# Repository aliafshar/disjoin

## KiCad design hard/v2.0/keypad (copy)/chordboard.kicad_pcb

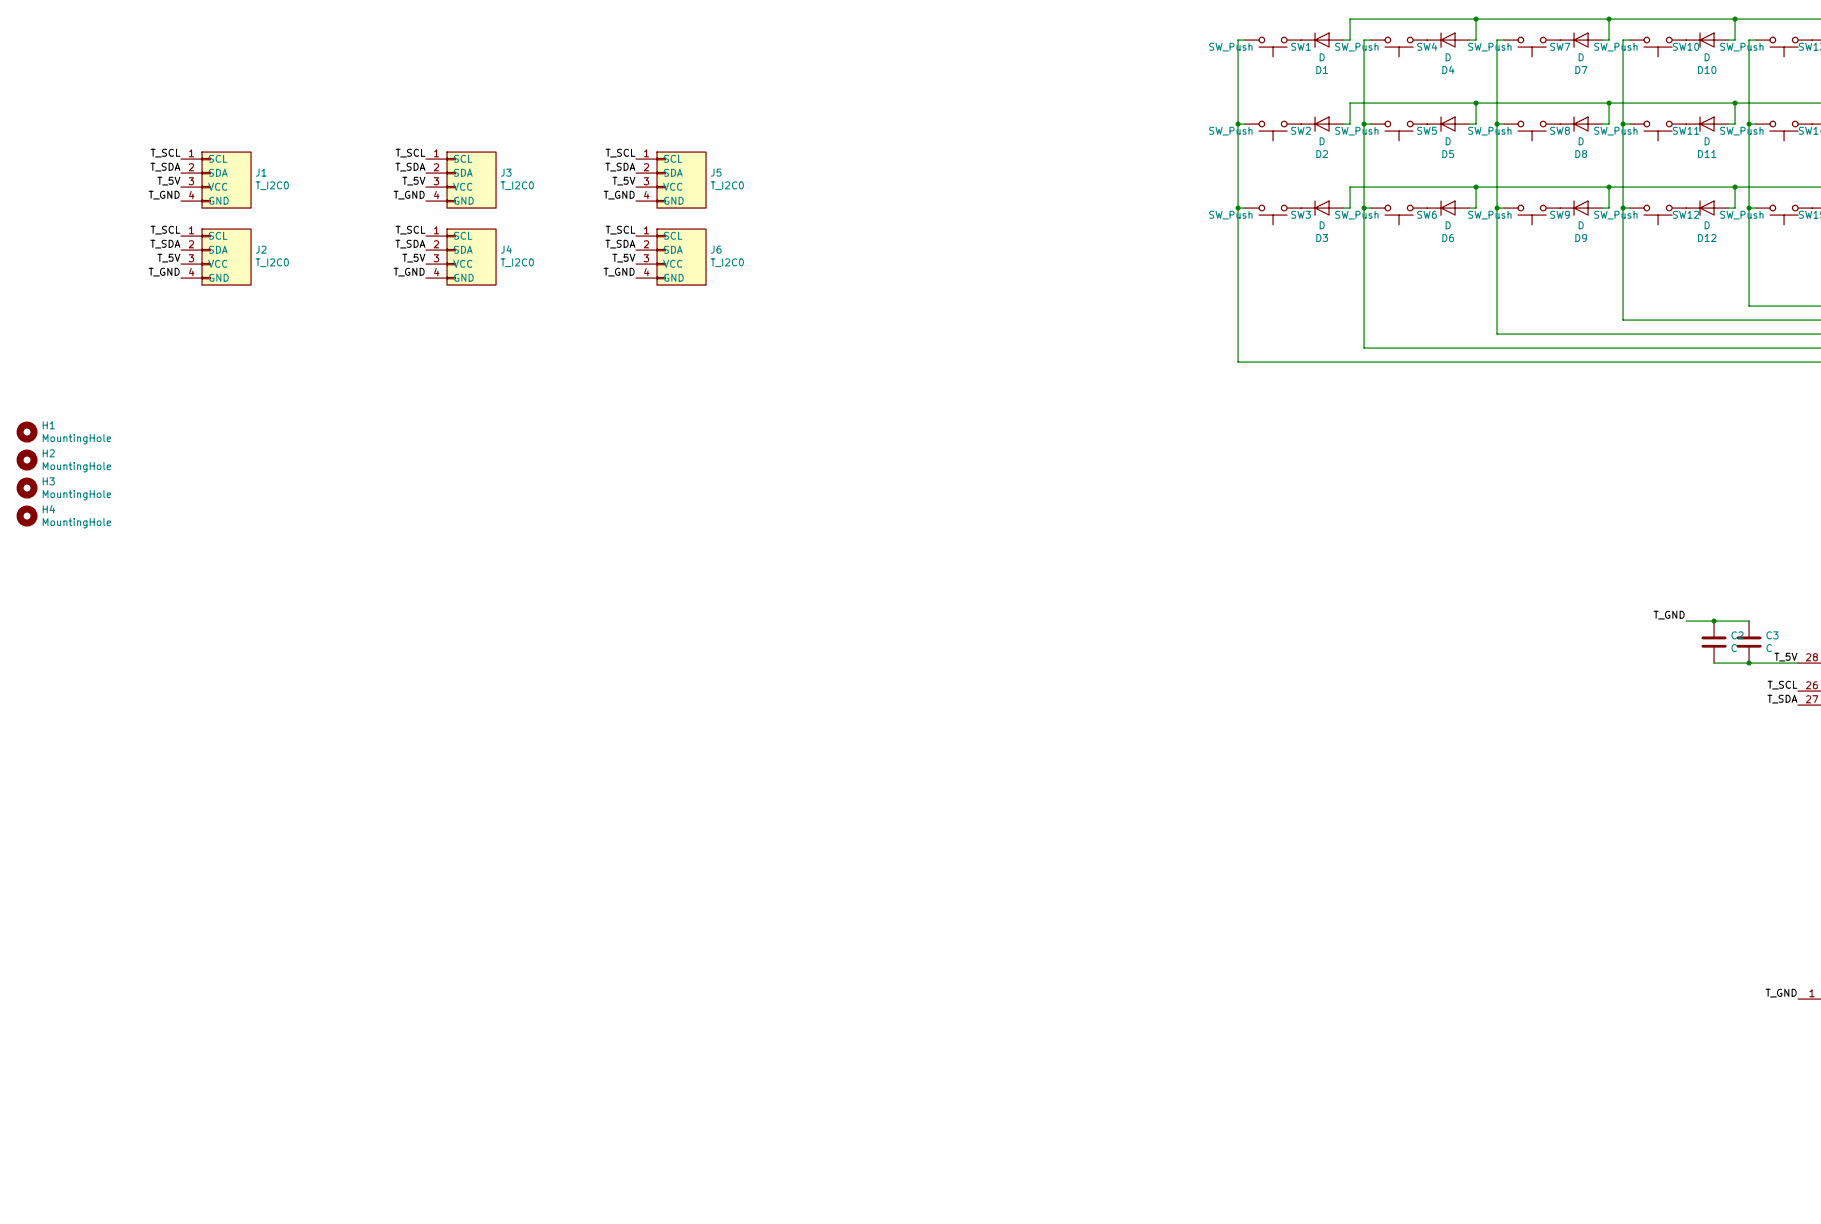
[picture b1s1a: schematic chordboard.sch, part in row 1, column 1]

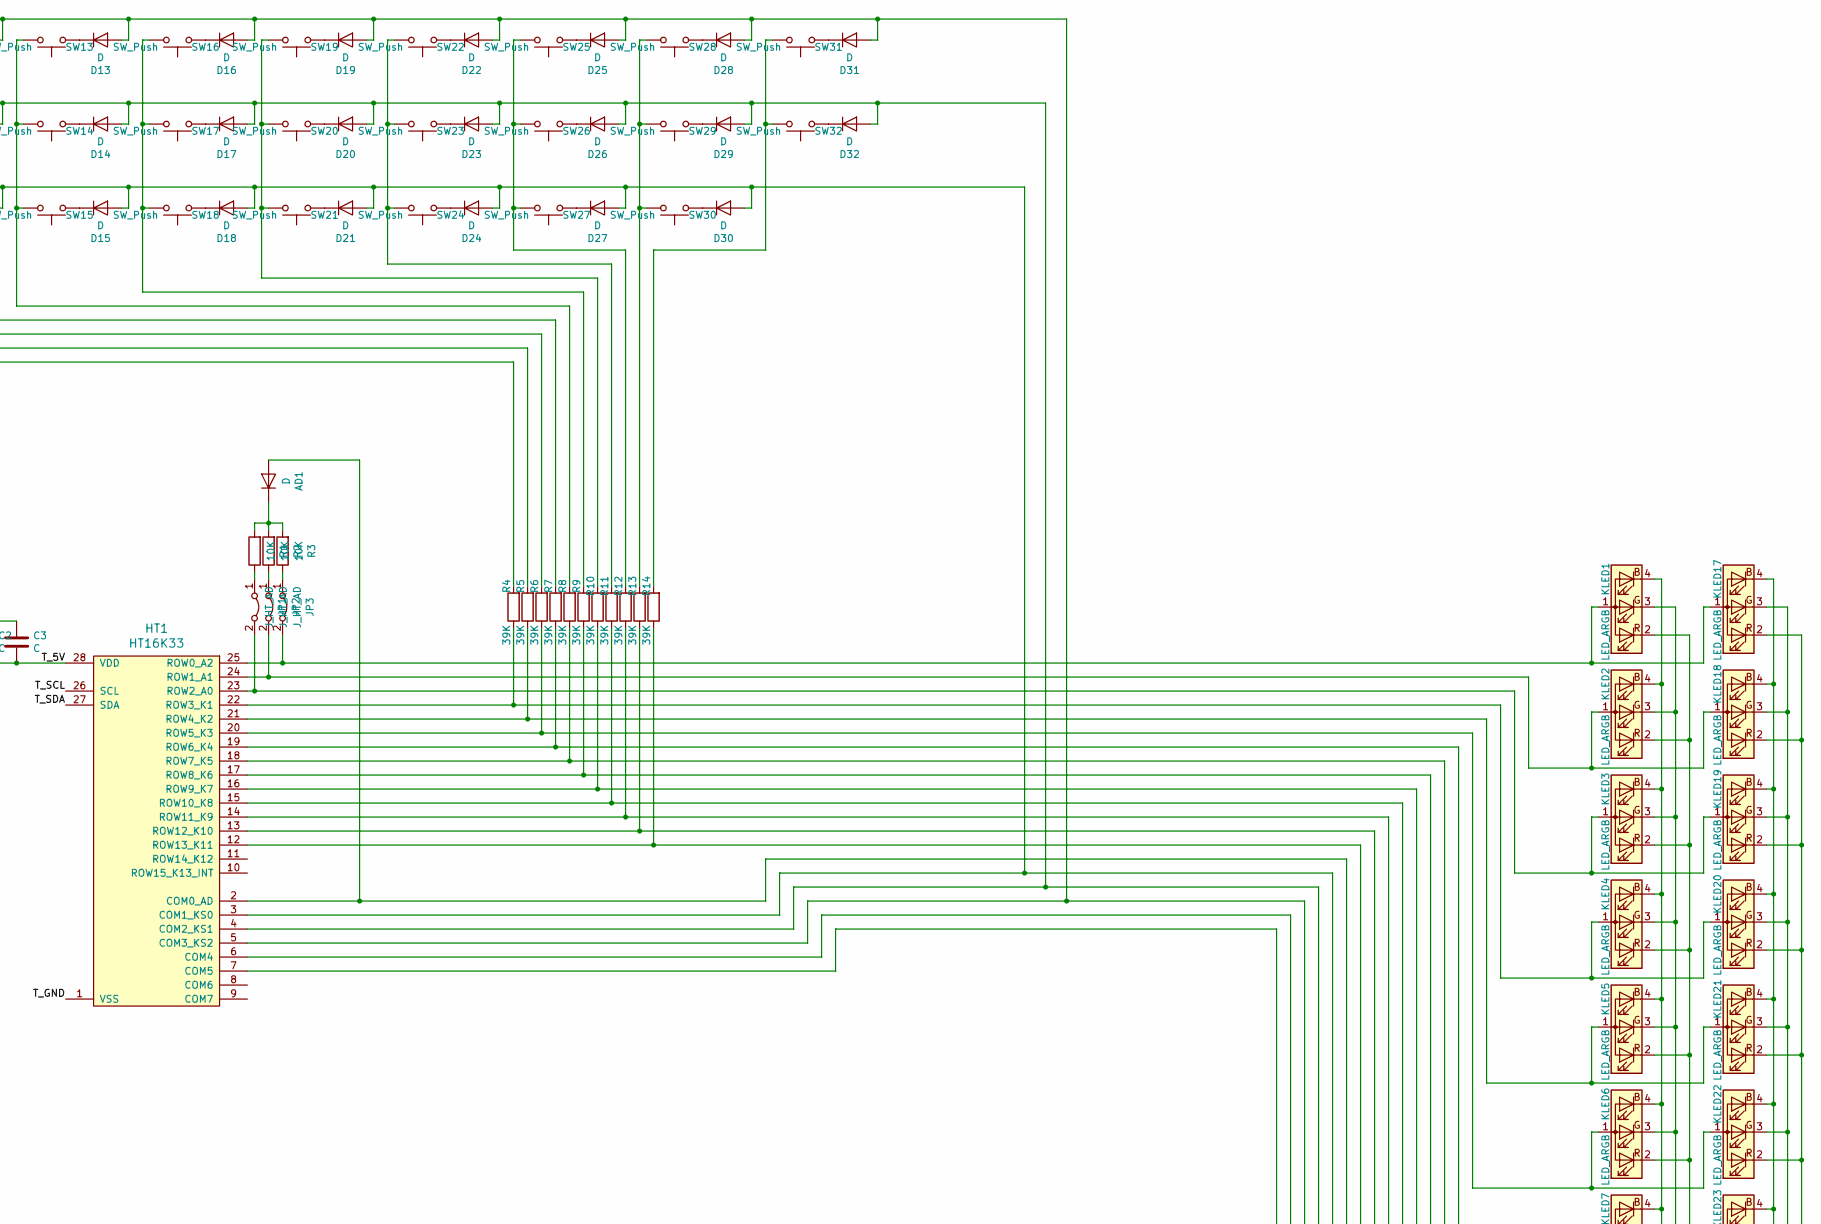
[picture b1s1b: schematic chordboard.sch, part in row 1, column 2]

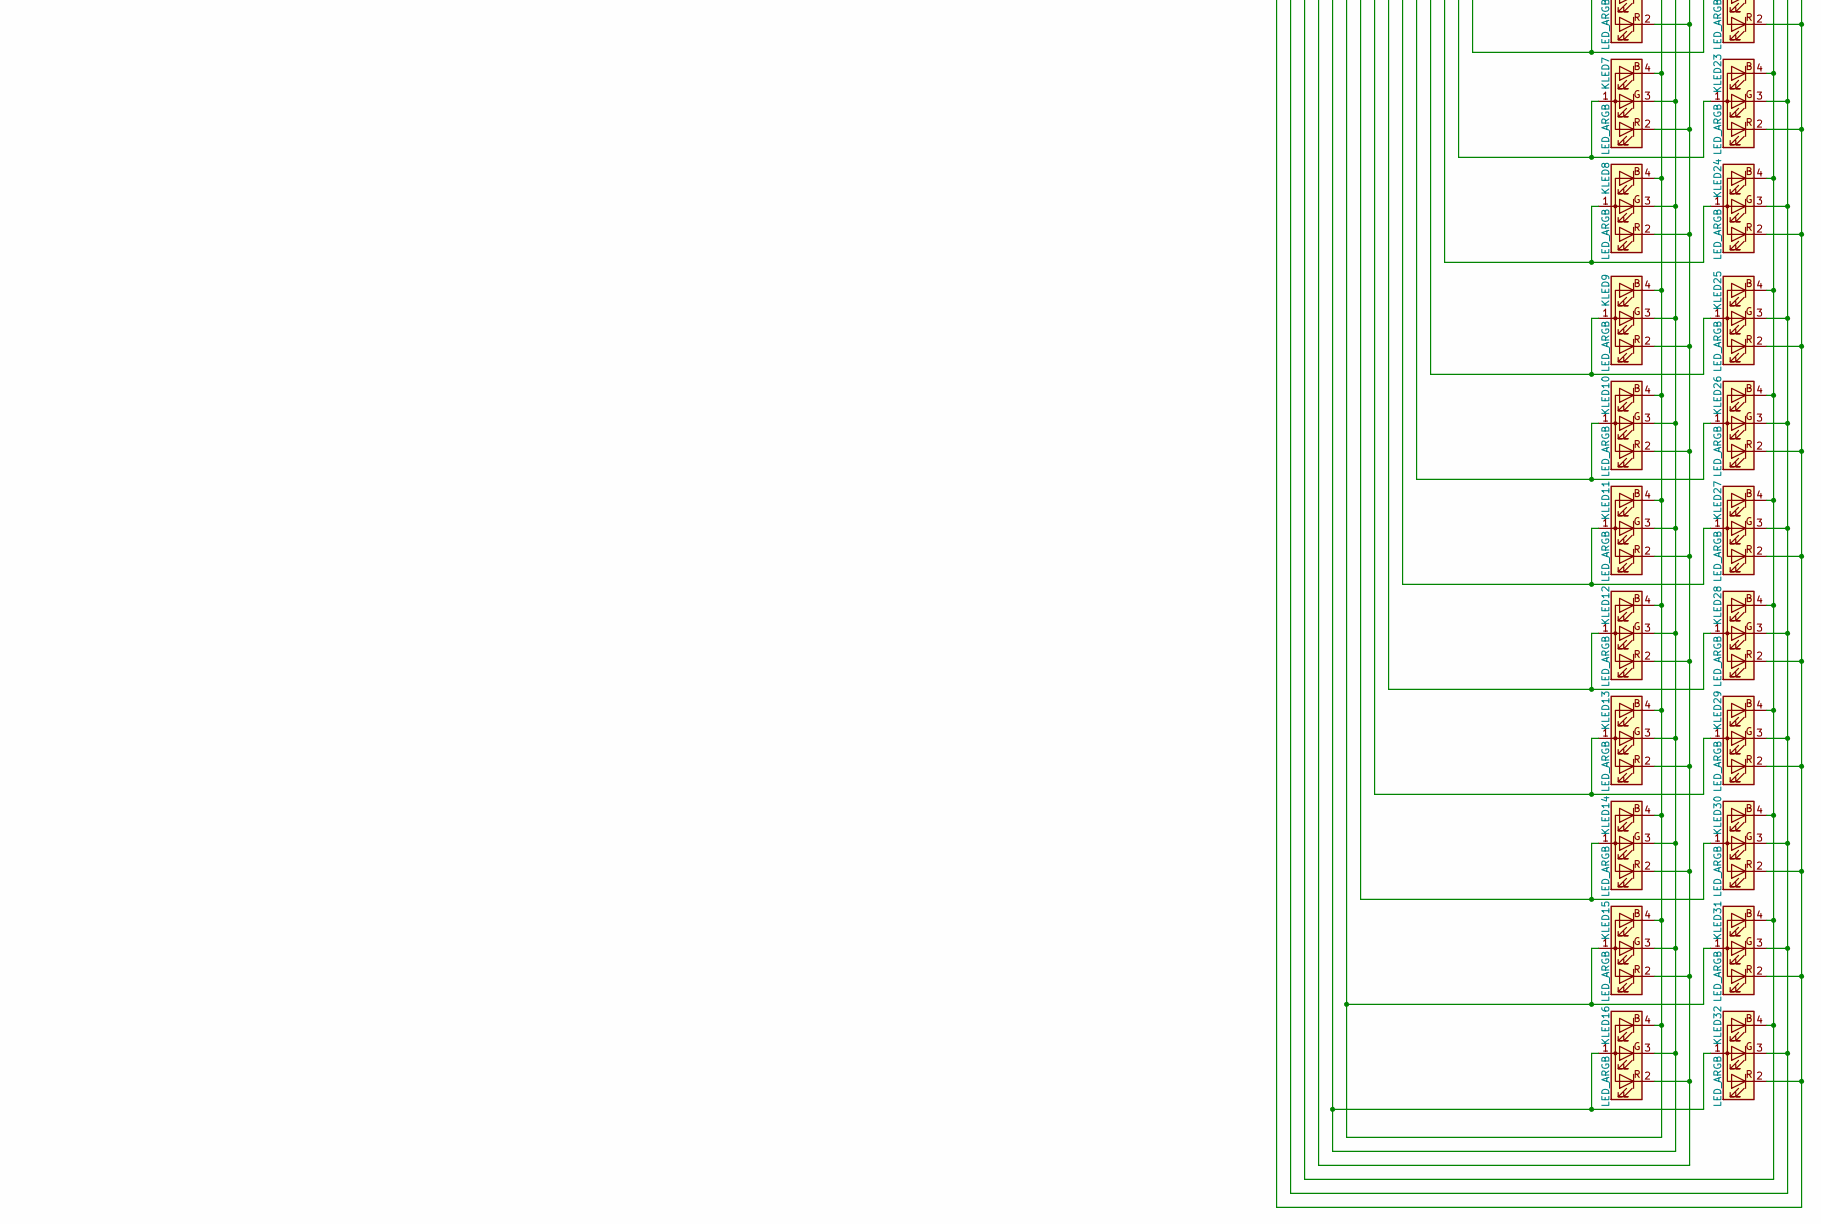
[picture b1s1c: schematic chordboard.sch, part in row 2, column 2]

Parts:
AD1: D; D_DO-41_SOD81_P7.62mm_Horizontal
C2, C3: C; C_Disc_D3.4mm_W2.1mm_P2.50mm
D1, D2, D3, D4, D5, D6, D7, D8, D9, D10, D11, D12, D13, D14, D15, D16, D17, D18, D19, D20, D21, D22, D23, D24, D25, D26, D27, D28, D29, D30, D31, D32: D; D_DO-41_SOD81_P7.62mm_Horizontal
H1, H2, H3, H4: MountingHole; MountingHole_2.7mm_M2.5_Pad_Via
HT1: HT16K33; SOIC-28W_7.5x17.9mm_P1.27mm
J1, J2, J3, J4: T_I2C0; JST_PH_B4B-PH-K_1x04_P2.00mm_Vertical
J5, J6: T_I2C0; PinHeader_1x04_P2.54mm_Vertical
JP1, JP2, JP3: J_HT_AD; SolderJumper-2_P1.3mm_Open_Pad1.0x1.5mm
KLED1, KLED2, KLED3, KLED4, KLED5, KLED6, KLED7, KLED8, KLED9, KLED10, KLED11, KLED12, KLED13, KLED14, KLED15, KLED16, KLED17, KLED18, KLED19, KLED20, KLED21, KLED22, KLED23, KLED24, KLED25, KLED26, KLED27, KLED28, KLED29, KLED30, KLED31, KLED32: LED_ARGB; LED_D3.0mm-4
R1, R2, R3: 10K; R_Axial_DIN0204_L3.6mm_D1.6mm_P5.08mm_Horizontal
R4, R5, R6, R7, R8, R9, R10, R11, R12, R13, R14: 39K; R_Axial_DIN0204_L3.6mm_D1.6mm_P5.08mm_Horizontal
SW1, SW2, SW3, SW4, SW5, SW6, SW7, SW8, SW9, SW10, SW11, SW12, SW13, SW14, SW15, SW16, SW17, SW18, SW19, SW20, SW21, SW22, SW23, SW24, SW25, SW26, SW27, SW28, SW29, SW30, SW31, SW32: SW_Push; CHERRY_PCB_100H

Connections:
/T_5V: C2.2, C3.2, HT1.28 (VDD), J1.3 (VCC), J2.3 (VCC), J3.3 (VCC), J4.3 (VCC), J5.3 (VCC), J6.3 (VCC)
/T_GND: C2.1, C3.1, HT1.1 (VSS), J1.4 (GND), J2.4 (GND), J3.4 (GND), J4.4 (GND), J5.4 (GND), J6.4 (GND)
/T_SCL: HT1.26 (SCL), J1.1 (SCL), J2.1 (SCL), J3.1 (SCL), J4.1 (SCL), J5.1 (SCL), J6.1 (SCL)
/T_SDA: HT1.27 (SDA), J1.2 (SDA), J2.2 (SDA), J3.2 (SDA), J4.2 (SDA), J5.2 (SDA), J6.2 (SDA)
unnamed: AD1.1 (K), R1.2, R2.2, R3.2
unnamed: AD1.2 (A), HT1.2 (COM0_AD), KLED1.4 (BK), KLED2.4 (BK), KLED3.4 (BK), KLED4.4 (BK), KLED5.4 (BK), KLED6.4 (BK), KLED7.4 (BK), KLED8.4 (BK), KLED9.4 (BK), KLED10.4 (BK), KLED11.4 (BK), KLED12.4 (BK), KLED13.4 (BK), KLED14.4 (BK), KLED15.1 (A), KLED15.4 (BK), KLED16.4 (BK), KLED31.1 (A)
unnamed: D1.1 (K), SW1.1
unnamed: D1.2 (A), D4.2 (A), D7.2 (A), D10.2 (A), D13.2 (A), D16.2 (A), D19.2 (A), D22.2 (A), D25.2 (A), D28.2 (A), D31.2 (A), HT1.5 (COM3_KS2), KLED17.4 (BK), KLED18.4 (BK), KLED19.4 (BK), KLED20.4 (BK), KLED21.4 (BK), KLED22.4 (BK), KLED23.4 (BK), KLED24.4 (BK), KLED25.4 (BK), KLED26.4 (BK), KLED27.4 (BK), KLED28.4 (BK), KLED29.4 (BK), KLED30.4 (BK), KLED31.4 (BK), KLED32.4 (BK)
unnamed: D2.1 (K), SW2.1
unnamed: D3.1 (K), SW3.1
unnamed: D4.1 (K), SW4.1
unnamed: D5.1 (K), SW5.1
unnamed: D6.1 (K), SW6.1
unnamed: D7.1 (K), SW7.1
unnamed: D8.1 (K), SW8.1
unnamed: D9.1 (K), SW9.1
unnamed: D10.1 (K), SW10.1
unnamed: D11.1 (K), SW11.1
unnamed: D2.2 (A), D5.2 (A), D8.2 (A), D11.2 (A), D14.2 (A), D17.2 (A), D20.2 (A), D23.2 (A), D26.2 (A), D29.2 (A), D32.2 (A), HT1.4 (COM2_KS1), KLED1.2 (RK), KLED2.2 (RK), KLED3.2 (RK), KLED4.2 (RK), KLED5.2 (RK), KLED6.2 (RK), KLED7.2 (RK), KLED8.2 (RK), KLED9.2 (RK), KLED10.2 (RK), KLED11.2 (RK), KLED12.2 (RK), KLED13.2 (RK), KLED14.2 (RK), KLED15.2 (RK), KLED16.2 (RK)
unnamed: D12.1 (K), SW12.1
unnamed: D3.2 (A), D6.2 (A), D9.2 (A), D12.2 (A), D15.2 (A), D18.2 (A), D21.2 (A), D24.2 (A), D27.2 (A), D30.2 (A), HT1.3 (COM1_KS0), KLED1.3 (GK), KLED2.3 (GK), KLED3.3 (GK), KLED4.3 (GK), KLED5.3 (GK), KLED6.3 (GK), KLED7.3 (GK), KLED8.3 (GK), KLED9.3 (GK), KLED10.3 (GK), KLED11.3 (GK), KLED12.3 (GK), KLED13.3 (GK), KLED14.3 (GK), KLED15.3 (GK), KLED16.1 (A), KLED16.3 (GK), KLED32.1 (A)
unnamed: D13.1 (K), SW13.1
unnamed: D14.1 (K), SW14.1
unnamed: D15.1 (K), SW15.1
unnamed: D16.1 (K), SW16.1
unnamed: D17.1 (K), SW17.1
unnamed: D18.1 (K), SW18.1
unnamed: D19.1 (K), SW19.1
unnamed: D20.1 (K), SW20.1
unnamed: D21.1 (K), SW21.1
unnamed: D22.1 (K), SW22.1
unnamed: D23.1 (K), SW23.1
unnamed: D24.1 (K), SW24.1
unnamed: D25.1 (K), SW25.1
unnamed: D26.1 (K), SW26.1
unnamed: D27.1 (K), SW27.1
unnamed: D28.1 (K), SW28.1
unnamed: D29.1 (K), SW29.1
unnamed: D30.1 (K), SW30.1
unnamed: D31.1 (K), SW31.1
unnamed: D32.1 (K), SW32.1
unnamed: HT1.6 (COM4), KLED17.3 (GK), KLED18.3 (GK), KLED19.3 (GK), KLED20.3 (GK), KLED21.3 (GK), KLED22.3 (GK), KLED23.3 (GK), KLED24.3 (GK), KLED25.3 (GK), KLED26.3 (GK), KLED27.3 (GK), KLED28.3 (GK), KLED29.3 (GK), KLED30.3 (GK), KLED31.3 (GK), KLED32.3 (GK)
unnamed: HT1.7 (COM5), KLED17.2 (RK), KLED18.2 (RK), KLED19.2 (RK), KLED20.2 (RK), KLED21.2 (RK), KLED22.2 (RK), KLED23.2 (RK), KLED24.2 (RK), KLED25.2 (RK), KLED26.2 (RK), KLED27.2 (RK), KLED28.2 (RK), KLED29.2 (RK), KLED30.2 (RK), KLED31.2 (RK), KLED32.2 (RK)
unnamed: HT1.12 (ROW13_K11), KLED14.1 (A), KLED30.1 (A), R14.1
unnamed: HT1.13 (ROW12_K10), KLED13.1 (A), KLED29.1 (A), R13.1
unnamed: HT1.14 (ROW11_K9), KLED12.1 (A), KLED28.1 (A), R12.1
unnamed: HT1.15 (ROW10_K8), KLED11.1 (A), KLED27.1 (A), R11.1
unnamed: HT1.16 (ROW9_K7), KLED10.1 (A), KLED26.1 (A), R10.1
unnamed: HT1.17 (ROW8_K6), KLED9.1 (A), KLED25.1 (A), R9.1
unnamed: HT1.18 (ROW7_K5), KLED8.1 (A), KLED24.1 (A), R8.1
unnamed: HT1.19 (ROW6_K4), KLED7.1 (A), KLED23.1 (A), R7.1
unnamed: HT1.20 (ROW5_K3), KLED6.1 (A), KLED22.1 (A), R6.1
unnamed: HT1.21 (ROW4_K2), KLED5.1 (A), KLED21.1 (A), R5.1
unnamed: HT1.22 (ROW3_K1), KLED4.1 (A), KLED20.1 (A), R4.1
unnamed: HT1.23 (ROW2_A0), JP1.2 (B), KLED3.1 (A), KLED19.1 (A)
unnamed: HT1.24 (ROW1_A1), JP2.2 (B), KLED2.1 (A), KLED18.1 (A)
unnamed: HT1.25 (ROW0_A2), JP3.2 (B), KLED1.1 (A), KLED17.1 (A)
unnamed: JP1.1 (A), R1.1
unnamed: JP2.1 (A), R2.1
unnamed: JP3.1 (A), R3.1
unnamed: R4.2, SW1.2, SW2.2, SW3.2
unnamed: R5.2, SW4.2, SW5.2, SW6.2
unnamed: R6.2, SW7.2, SW8.2, SW9.2
unnamed: R7.2, SW10.2, SW11.2, SW12.2
unnamed: R8.2, SW13.2, SW14.2, SW15.2
unnamed: R9.2, SW16.2, SW17.2, SW18.2
unnamed: R10.2, SW19.2, SW20.2, SW21.2
unnamed: R11.2, SW22.2, SW23.2, SW24.2
unnamed: R12.2, SW25.2, SW26.2, SW27.2
unnamed: R13.2, SW28.2, SW29.2, SW30.2
unnamed: R14.2, SW31.2, SW32.2

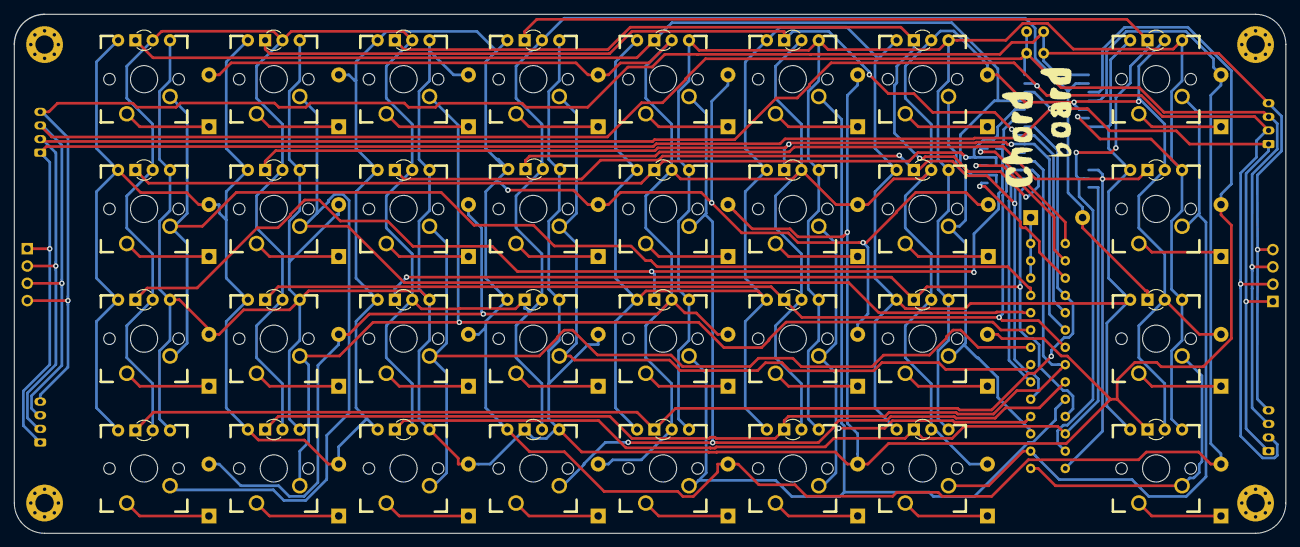
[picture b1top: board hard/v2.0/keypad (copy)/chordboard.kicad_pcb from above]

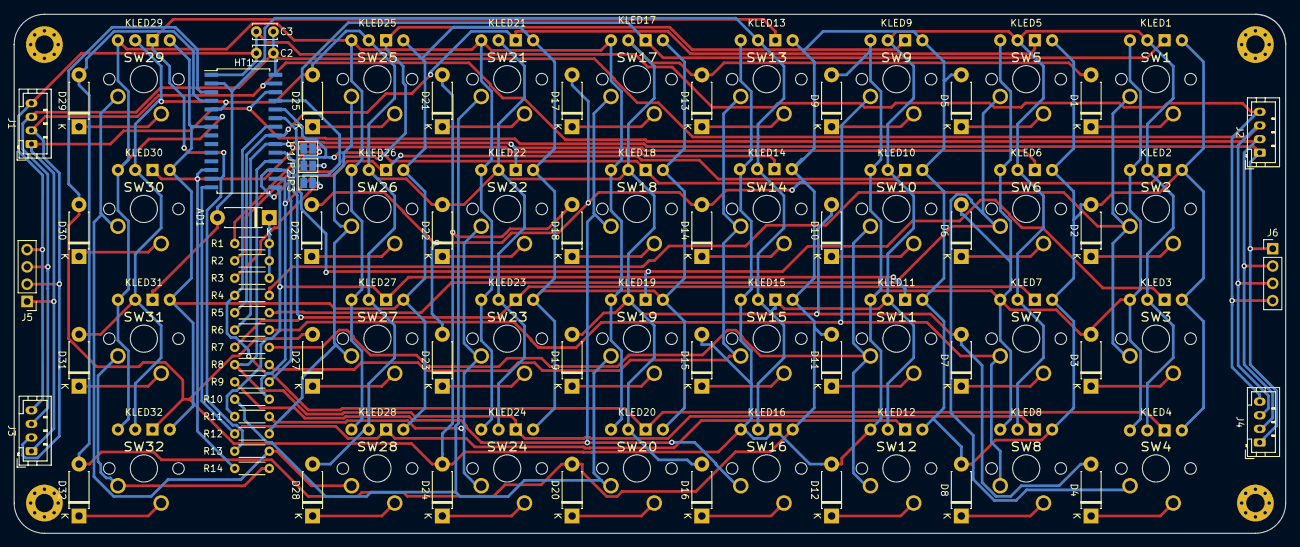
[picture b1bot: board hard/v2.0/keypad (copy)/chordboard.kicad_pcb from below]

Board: 2 copper layers, 186.7 x 76.2 mm, 127 parts (59 on the bottom side), 71 nets.

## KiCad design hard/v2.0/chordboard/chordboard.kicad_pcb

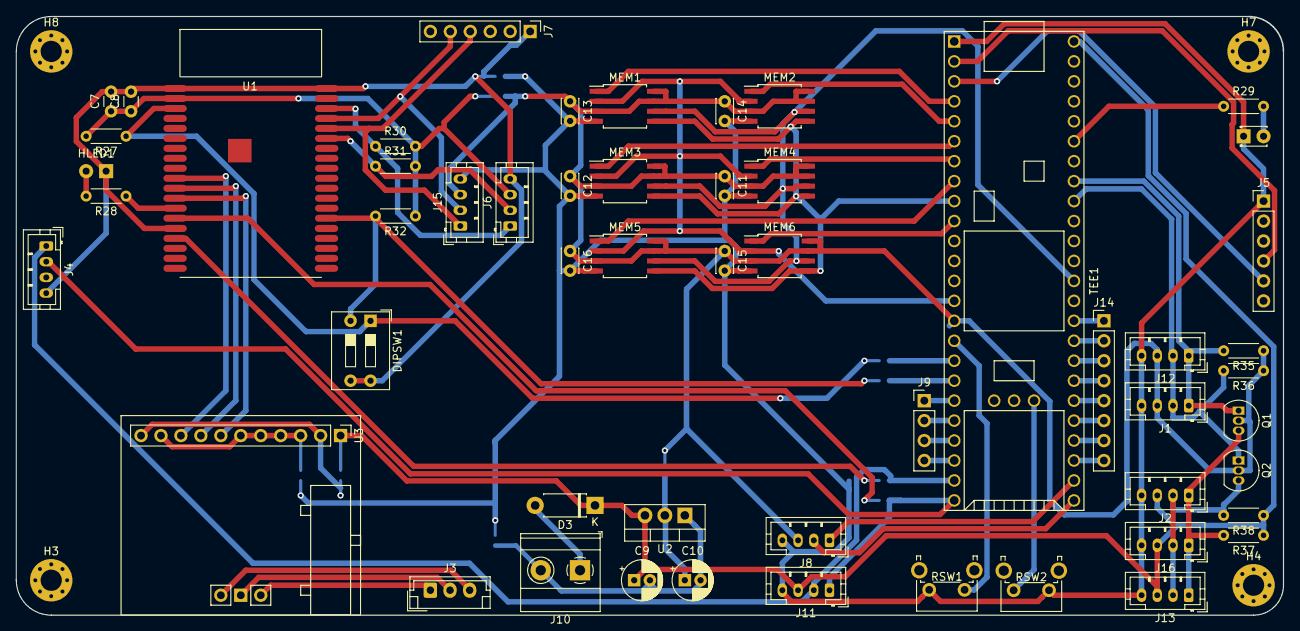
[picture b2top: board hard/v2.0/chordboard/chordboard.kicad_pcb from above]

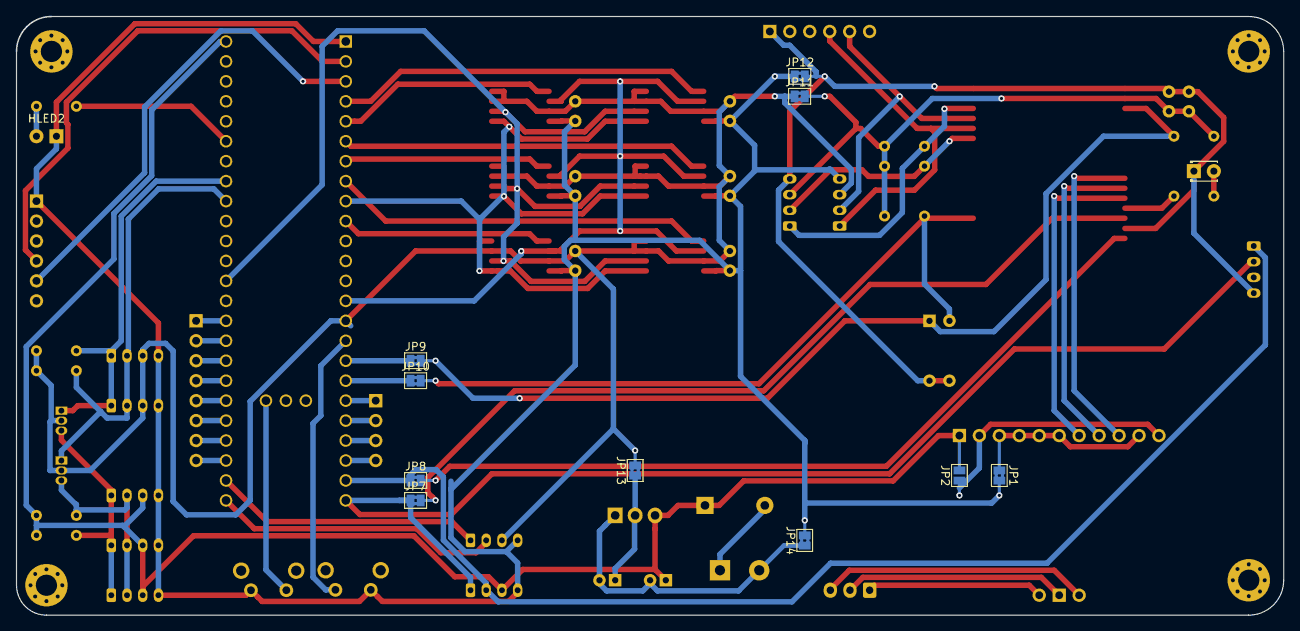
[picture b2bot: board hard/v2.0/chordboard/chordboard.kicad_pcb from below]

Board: 2 copper layers, 161.3 x 76.2 mm, 68 parts (11 on the bottom side), 63 nets.

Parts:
C7, C8: C; C_Disc_D3.0mm_W1.6mm_P2.50mm
C9: 10uF; CP_Radial_D5.0mm_P2.00mm
C10: 100uF; CP_Radial_D5.0mm_P2.00mm
C11, C12, C13, C14, C15, C16: C_Small; C_Disc_D3.0mm_W2.0mm_P2.50mm
D3: D; D_DO-41_SOD81_P7.62mm_Horizontal
DIPSW1: E_BOOTOPTS; SW_DIP_SPSTx02_Slide_9.78x7.26mm_W7.62mm_P2.54mm
H3, H4, H7, H8: MountingHole; MountingHole_2.7mm_M2.5_Pad_Via
HLED1: E_HEARTBEAT; LED_D1.8mm_W3.3mm_H2.4mm
HLED2: T_HEARTBEAT; LED_D1.8mm_W3.3mm_H2.4mm
J1, J12: T_I2C0_3V; JST_PH_B4B-PH-K_1x04_P2.00mm_Vertical
J2, J13, J16: T_I2C0_5V; JST_PH_B4B-PH-K_1x04_P2.00mm_Vertical
J3: Conn_01x03; JST_EH_B03B-EH-A_1x03_P2.50mm_Vertical
J4: E_UART2; JST_PH_B4B-PH-K_1x04_P2.00mm_Vertical
J5: T_UART0; PinHeader_1x06_P2.54mm_Vertical
J6: E_I2C0; JST_PH_B4B-PH-K_1x04_P2.00mm_Vertical
J7: E_UART0; PinHeader_1x06_P2.54mm_Vertical
J8: T_UART5; JST_PH_B4B-PH-K_1x04_P2.00mm_Vertical
J9: Conn_01x04; PinHeader_1x04_P2.54mm_Vertical
J10: ++5V_IN; TerminalBlock_Phoenix_MKDS-1,5-2_1x02_P5.00mm_Horizontal
J11: T_UART4; JST_PH_B4B-PH-K_1x04_P2.00mm_Vertical
J14: Conn_01x08; PinHeader_1x08_P2.54mm_Vertical
J15: E_UART1; JST_PH_B4B-PH-K_1x04_P2.00mm_Vertical
JP1, JP12: Jumper_2_Bridged; SolderJumper-2_P1.3mm_Bridged2Bar_Pad1.0x1.5mm
JP2: Jumper_2_Open; SolderJumper-2_P1.3mm_Open_Pad1.0x1.5mm
JP7: J_ESP_RX2; SolderJumper-2_P1.3mm_Bridged2Bar_Pad1.0x1.5mm
JP8: J_ESP_TX2; SolderJumper-2_P1.3mm_Bridged2Bar_Pad1.0x1.5mm
JP9: J_ESP_RST; SolderJumper-2_P1.3mm_Bridged2Bar_Pad1.0x1.5mm
JP10: J_ESP_D0; SolderJumper-2_P1.3mm_Bridged2Bar_Pad1.0x1.5mm
JP11: J_ESP_3V3; SolderJumper-2_P1.3mm_Bridged2Bar_Pad1.0x1.5mm
JP13: J_PWR_3V3; SolderJumper-2_P1.3mm_Bridged2Bar_Pad1.0x1.5mm
JP14: J_PWR_GND; SolderJumper-2_P1.3mm_Bridged2Bar_Pad1.0x1.5mm
MEM1, MEM2, MEM3, MEM4, MEM5, MEM6: 23LC1024; SOIJ-8_5.3x5.3mm_P1.27mm
Q1, Q2: 2N7000; TO-92_Inline
R27, R32: 10K; R_Axial_DIN0204_L3.6mm_D1.6mm_P5.08mm_Horizontal
R28, R29: 200; R_Axial_DIN0204_L3.6mm_D1.6mm_P5.08mm_Horizontal
R30, R31: 4.7K; R_Axial_DIN0204_L3.6mm_D1.6mm_P5.08mm_Horizontal
R35, R36, R37, R38: R; R_Axial_DIN0204_L3.6mm_D1.6mm_P5.08mm_Horizontal
RSW1: E_PGM; SW_Tactile_SPST_Angled_PTS645Vx58-2LFS
RSW2: T_PGM; SW_Tactile_SPST_Angled_PTS645Vx58-2LFS
TEE1: Teensy3.6; teensy36
U1: ESP32-WROVER
U2: AZ1117-3.3; TO-220-3_Vertical
U3: DMPCM5102; DMPCM5102_BLACK

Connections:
+3V3: C10.1, JP13.1, U2.2
+5V: C9.1, D3.1, J2.3, J11.3, J13.3, J16.3, JP2.2, R37.1, R38.1, TEE1.48, U2.3, U3.1
/DAC_3V3: JP2.1, U3.2, U3.11
/DAC_GND: JP1.1, U3.3, U3.4, U3.5, U3.6, U3.10
/ESP_3V3: C7.1, C8.1, J6.3, JP11.2, R27.2, R30.2, R31.2, R32.1, U1.2
/ESP_D0: DIPSW1.2, JP10.2, R32.2, U1.25
/ESP_GND: C7.2, C8.2, DIPSW1.3, DIPSW1.4, HLED1.1, J4.4, J6.4, J7.1, JP12.2, U1.1, U1.15, U1.38
/ESP_RST: DIPSW1.1, JP9.2, R27.1, U1.3
/ESP_RX0: J7.4, J15.1, U1.34
/ESP_RX2: JP7.2, U1.14
/ESP_SCL: J6.1, R30.1, U1.36
/ESP_SDA: J6.2, R31.1, U1.33
/ESP_TX0: J7.5, J15.2, U1.35
/ESP_TX2: JP8.2, U1.16
/MEMCARD_CS1: MEM1.1, TEE1.4
/MEMCARD_CS2: MEM2.1, TEE1.5
/MEMCARD_CS3: MEM3.1, TEE1.6
/MEMCARD_CS4: MEM4.1, TEE1.7
/MEMCARD_CS5: MEM5.1, TEE1.8
/MEMCARD_CS6: MEM6.1, TEE1.10
/MEMCARD_MISO: MEM1.2, MEM2.2, MEM3.2, MEM4.2, MEM5.2, MEM6.2, TEE1.14
/MEMCARD_MOSI: MEM1.5, MEM2.5, MEM3.5, MEM4.5, MEM5.5, MEM6.5, TEE1.9
/MEMCARD_SCK: MEM1.6, MEM2.6, MEM3.6, MEM4.6, MEM5.6, MEM6.6, TEE1.36
/RX5: J8.1, TEE1.26
/TX5: J8.2, TEE1.25
/T_3V3: C11.1, C12.1, C13.1, C14.1, C15.1, C16.1, J1.3, J8.3, J12.3, J15.3, JP11.1, JP13.2, MEM1.3, MEM1.7, MEM1.8, MEM2.3, MEM2.7, MEM2.8, MEM3.3, MEM3.7, MEM3.8, MEM4.3, MEM4.7, MEM4.8, MEM5.3, MEM5.7, MEM5.8, MEM6.3, MEM6.7, MEM6.8, Q1.2, Q2.2, R35.1, R36.1, TEE1.15
/T_GND: C11.2, C12.2, C13.2, C14.2, C15.2, C16.2, HLED2.1, J1.4, J2.4, J5.1, J8.4, J11.4, J12.4, J13.4, J15.4, J16.4, JP1.2, JP12.1, JP14.2, MEM1.4, MEM2.4, MEM3.4, MEM4.4, MEM5.4, MEM6.4, RSW1.2, RSW2.1, TEE1.1
/T_PGM: RSW2.2, TEE1.51
/T_RX1: J5.4, TEE1.2
/T_RX4: J4.1, J11.2, JP8.1, TEE1.23
/T_SCL: J1.1, J12.1, Q1.1, R35.2, TEE1.41
/T_SCL5: J2.1, J13.1, J16.1, Q1.3, R37.2
/T_SDA: J1.2, J12.2, Q2.1, R36.2, TEE1.40
/T_SDA5: J2.2, J13.2, J16.2, Q2.3, R38.2
/T_TX1: J5.5, TEE1.3
/T_TX4: J4.2, J11.1, JP7.1, TEE1.24
GND: C9.2, C10.2, J10.2, JP14.1, U2.1
unnamed: D3.2, J10.1
unnamed: HLED1.2, R28.2
unnamed: HLED2.2, R29.2
unnamed: J3.1, U3.12
unnamed: J3.2, U3.13
unnamed: J3.3, U3.14
unnamed: J9.1, TEE1.19
unnamed: J9.2, TEE1.20
unnamed: J9.3, TEE1.21
unnamed: J9.4, TEE1.22
unnamed: J14.1, TEE1.34
unnamed: J14.2, TEE1.33
unnamed: J14.3, TEE1.32
unnamed: J14.4, TEE1.31
unnamed: J14.5, TEE1.30
unnamed: J14.6, TEE1.29
unnamed: J14.7, TEE1.28
unnamed: J14.8, TEE1.27
unnamed: JP9.1, TEE1.17
unnamed: JP10.1, TEE1.18
unnamed: R28.1, U1.13
unnamed: R29.1, TEE1.43
unnamed: RSW1.1, TEE1.16
unnamed: U1.10, U3.9
unnamed: U1.11, U3.8
unnamed: U1.12, U3.7

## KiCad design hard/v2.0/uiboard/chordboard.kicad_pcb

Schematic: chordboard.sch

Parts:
C1, C2, C3: C_0.1uF; C_0402_1005Metric
C4: CP_10uF; CP_EIA-3216-18_Kemet-A
D1, D2, D3, D4, D5, D6, D7, D8, D9, D10, D11, D12, D13, D14, D15, D16, D17, D18, D19, D20, D21, D22, D23, D24, D25, D26, D27, D28, D29, D30, D31, D32, D33, D34, D35, D36, D37, D38, D39, D40, D41, D42, D43, D44, D45, D46, D47, D48, D49, D50, D51, D52, D53, D54, D55, D56, D57, D58, D59, D60, D61, D62, D63, D64, D65, D66, D67, D68, D69, D70, D71, D72, D73, D74, D75, D76, D77, D78, D79, D80, D81, D82, D83, D84, D85, D86, D87, D88, D89, D90, D91, D92, D93, D94, D95, D96, D97, D98, D99, D100, D101, D102, D103, D104, D105, D106, D107, D108, D109, D110, D111, D112, D113, D114, D115, D116, D117, D118, D119, D120, D121, D122, D123, D124, D125, D126, D127, D128: LED_RED; LED_0603_1608Metric_Castellated
D129: D_1N4148WS; D_SOD-323F
H1, H2, H3, H4: MountingHole; MountingHole_2.2mm_M2_Pad_Via
HT1: HT16K33; SOIC-28W_7.5x17.9mm_P1.27mm
J2, J3: T_I2C0; JST_PH_B4B-PH-K_1x04_P2.00mm_Vertical
PLED1: LED_RED; LED_0603_1608Metric_Castellated
R1, R2, R3, R4, R5, R6: R_10K; R_0402_1005Metric
R7: R_330R; R_0402_1005Metric
SW1, SW2, SW3, SW4, SW5, SW6, SW7, SW8, SW9, SW10, SW11, SW12, SW13, SW14, SW15, SW16: SW_Push; SW_Cherry_MX_1.00u_PCB
SWA1, SWA2: SW_DIP_x03; SW_DIP_SPSTx03_Slide_9.78x9.8mm_W7.62mm_P2.54mm
U1: MCP23017_SO; SOIC-28W_7.5x17.9mm_P1.27mm

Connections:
+5V: C1.2, C2.2, C3.2, C4.1, HT1.28 (VDD), J2.3 (VCC), J3.3 (VCC), R7.2, SWA1.1, SWA1.2, SWA1.3, U1.9 (VDD), U1.18 (~RESET~)
/SCL5: HT1.26 (SCL), J2.1 (SCL), J3.1 (SCL), U1.12 (SCK)
/SDA5: HT1.27 (SDA), J2.2 (SDA), J3.2 (SDA), U1.13 (SDA)
GND: C1.1, C2.1, C3.1, C4.2, HT1.1 (VSS), J2.4 (GND), J3.4 (GND), PLED1.1 (K), R4.2, R5.2, R6.2, SW1.2, SW2.2, SW3.2, SW4.2, SW5.2, SW6.2, SW7.2, SW8.2, SW9.2, SW10.2, SW11.2, SW12.2, SW13.2, SW14.2, SW15.2, SW16.2, U1.10 (VSS)
unnamed: D1.1 (K), D2.1 (K), D3.1 (K), D4.1 (K), D5.1 (K), D6.1 (K), D7.1 (K), D8.1 (K), D9.1 (K), D10.1 (K), D11.1 (K), D12.1 (K), D13.1 (K), D14.1 (K), D15.1 (K), D16.1 (K), D129.2 (A), HT1.2 (COM0_AD)
unnamed: D1.2 (A), D17.2 (A), D33.2 (A), D49.2 (A), D65.2 (A), D81.2 (A), D97.2 (A), D113.2 (A), HT1.25 (ROW0_A2), SWA2.6
unnamed: D10.2 (A), D26.2 (A), D42.2 (A), D58.2 (A), D74.2 (A), D90.2 (A), D106.2 (A), D122.2 (A), HT1.16 (ROW9_K7)
unnamed: D17.1 (K), D18.1 (K), D19.1 (K), D20.1 (K), D21.1 (K), D22.1 (K), D23.1 (K), D24.1 (K), D25.1 (K), D26.1 (K), D27.1 (K), D28.1 (K), D29.1 (K), D30.1 (K), D31.1 (K), D32.1 (K), HT1.3 (COM1_KS0)
unnamed: D33.1 (K), D34.1 (K), D35.1 (K), D36.1 (K), D37.1 (K), D38.1 (K), D39.1 (K), D40.1 (K), D41.1 (K), D42.1 (K), D43.1 (K), D44.1 (K), D45.1 (K), D46.1 (K), D47.1 (K), D48.1 (K), HT1.4 (COM2_KS1)
unnamed: D49.1 (K), D50.1 (K), D51.1 (K), D52.1 (K), D53.1 (K), D54.1 (K), D55.1 (K), D56.1 (K), D57.1 (K), D58.1 (K), D59.1 (K), D60.1 (K), D61.1 (K), D62.1 (K), D63.1 (K), D64.1 (K), HT1.5 (COM3_KS2)
unnamed: D65.1 (K), D66.1 (K), D67.1 (K), D68.1 (K), D69.1 (K), D70.1 (K), D71.1 (K), D72.1 (K), D73.1 (K), D74.1 (K), D75.1 (K), D76.1 (K), D77.1 (K), D78.1 (K), D79.1 (K), D80.1 (K), HT1.6 (COM4)
unnamed: D81.1 (K), D82.1 (K), D83.1 (K), D84.1 (K), D85.1 (K), D86.1 (K), D87.1 (K), D88.1 (K), D89.1 (K), D90.1 (K), D91.1 (K), D92.1 (K), D93.1 (K), D94.1 (K), D95.1 (K), D96.1 (K), HT1.7 (COM5)
unnamed: D97.1 (K), D98.1 (K), D99.1 (K), D100.1 (K), D101.1 (K), D102.1 (K), D103.1 (K), D104.1 (K), D105.1 (K), D106.1 (K), D107.1 (K), D108.1 (K), D109.1 (K), D110.1 (K), D111.1 (K), D112.1 (K), HT1.8 (COM6)
unnamed: D4.2 (A), D20.2 (A), D36.2 (A), D52.2 (A), D68.2 (A), D84.2 (A), D100.2 (A), D116.2 (A), HT1.22 (ROW3_K1)
unnamed: D5.2 (A), D21.2 (A), D37.2 (A), D53.2 (A), D69.2 (A), D85.2 (A), D101.2 (A), D117.2 (A), HT1.21 (ROW4_K2)
unnamed: D6.2 (A), D22.2 (A), D38.2 (A), D54.2 (A), D70.2 (A), D86.2 (A), D102.2 (A), D118.2 (A), HT1.20 (ROW5_K3)
unnamed: D7.2 (A), D23.2 (A), D39.2 (A), D55.2 (A), D71.2 (A), D87.2 (A), D103.2 (A), D119.2 (A), HT1.19 (ROW6_K4)
unnamed: D8.2 (A), D24.2 (A), D40.2 (A), D56.2 (A), D72.2 (A), D88.2 (A), D104.2 (A), D120.2 (A), HT1.18 (ROW7_K5)
unnamed: D9.2 (A), D25.2 (A), D41.2 (A), D57.2 (A), D73.2 (A), D89.2 (A), D105.2 (A), D121.2 (A), HT1.17 (ROW8_K6)
unnamed: D11.2 (A), D27.2 (A), D43.2 (A), D59.2 (A), D75.2 (A), D91.2 (A), D107.2 (A), D123.2 (A), HT1.15 (ROW10_K8)
unnamed: D12.2 (A), D28.2 (A), D44.2 (A), D60.2 (A), D76.2 (A), D92.2 (A), D108.2 (A), D124.2 (A), HT1.14 (ROW11_K9)
unnamed: D13.2 (A), D29.2 (A), D45.2 (A), D61.2 (A), D77.2 (A), D93.2 (A), D109.2 (A), D125.2 (A), HT1.13 (ROW12_K10)
unnamed: D14.2 (A), D30.2 (A), D46.2 (A), D62.2 (A), D78.2 (A), D94.2 (A), D110.2 (A), D126.2 (A), HT1.12 (ROW13_K11)
unnamed: D15.2 (A), D31.2 (A), D47.2 (A), D63.2 (A), D79.2 (A), D95.2 (A), D111.2 (A), D127.2 (A), HT1.11 (ROW14_K12)
unnamed: D16.2 (A), D32.2 (A), D48.2 (A), D64.2 (A), D80.2 (A), D96.2 (A), D112.2 (A), D128.2 (A), HT1.10 (ROW15_K13_INT)
unnamed: D113.1 (K), D114.1 (K), D115.1 (K), D116.1 (K), D117.1 (K), D118.1 (K), D119.1 (K), D120.1 (K), D121.1 (K), D122.1 (K), D123.1 (K), D124.1 (K), D125.1 (K), D126.1 (K), D127.1 (K), D128.1 (K), HT1.9 (COM7)
unnamed: D2.2 (A), D18.2 (A), D34.2 (A), D50.2 (A), D66.2 (A), D82.2 (A), D98.2 (A), D114.2 (A), HT1.24 (ROW1_A1), SWA2.5
unnamed: D3.2 (A), D19.2 (A), D35.2 (A), D51.2 (A), D67.2 (A), D83.2 (A), D99.2 (A), D115.2 (A), HT1.23 (ROW2_A0), SWA2.4
unnamed: D129.1 (K), R1.1, R2.1, R3.1
unnamed: PLED1.2 (A), R7.1
unnamed: R1.2, SWA2.3
unnamed: R2.2, SWA2.2
unnamed: R3.2, SWA2.1
unnamed: R4.1, SWA1.6, U1.17 (A2)
unnamed: R5.1, SWA1.5, U1.16 (A1)
unnamed: R6.1, SWA1.4, U1.15 (A0)
unnamed: SW1.1, U1.1 (GPB0)
unnamed: SW2.1, U1.2 (GPB1)
unnamed: SW3.1, U1.3 (GPB2)
unnamed: SW4.1, U1.4 (GPB3)
unnamed: SW5.1, U1.5 (GPB4)
unnamed: SW6.1, U1.6 (GPB5)
unnamed: SW7.1, U1.7 (GPB6)
unnamed: SW8.1, U1.8 (GPB7)
unnamed: SW9.1, U1.21 (GPA0)
unnamed: SW10.1, U1.22 (GPA1)
unnamed: SW11.1, U1.23 (GPA2)
unnamed: SW12.1, U1.24 (GPA3)
unnamed: SW13.1, U1.25 (GPA4)
unnamed: SW14.1, U1.26 (GPA5)
unnamed: SW15.1, U1.27 (GPA6)
unnamed: SW16.1, U1.28 (GPA7)
